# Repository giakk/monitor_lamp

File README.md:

# Monitor Light Bar

## Overview
I wanted a smart monitor bar without spending hundreds of euros for something like the BenQ monitor lamp, so I tried to DIY it. Everithing runs on an ESP32-C3 microcontroller, a bit overkill but it will be useful for future upgrade. To control the led, the ESP32 rely on two sensors: a VELM7700 luminosity sensor to dynamically adjusts the leds brightness to maintain optimal lighting conditions, and a LD2410 presense sensor to automatically activates when a user sits.

## 3D Design

## Electronics
The system is powered by a 12V input managed via a USB-C Power Delivery (PD) controller, which negotiate with the power supply to ensures 12V for the leds strips. A Mini360 step-down converter reduces this voltage to 5V to power the ESP32-C3 and the sensors, while a dedicated 1.25A fuse protects the entire circuit. The light engine consists of a 12V LED strip driven by an IRLZ44N MOSFET, which allows for precise PWM dimming controlled by the ESP32.

The "intelligence" of the hardware relies on two main modules: an LD2410 presence sensor connected via UART and a VEML7700 ambient light sensor communicating through the I2C protocol. 
The current prototype, as shown in the images below was updated with the new custom developed PCB board, which info can be found in the Kicad project. (Yeah, I know it is overkill but why no? I wanted to learn to use Kicad and develop my first PCB)

|  |  |
|:---:|:---:|

The board has been tested and corrected due to two mistakes I made in the eletrical scheme. First, I hadn't included the ISET resistor for the PD controller, which is essential for negotiating the correct voltage with the charger. Second, I had swapped the drain and source pins of the Q3 MOSFET. Now that everything works as expected, the board project should be correct I you want to produce it.

## Code
The firmware is developed within the Arduino framework and utilizes a non-blocking logic to monitor environmental changes in real-time. The core functionality revolves around an adaptive dimming algorithm: the system reads the ambient lux levels via the VEML7700 and applies a square root function to calculate the ideal LED duty cycle. This function actually work like the luminosity on the phone, so it increase if the lux of the room are high, while decrease if there is not light in the room. Maybe it is counterintuitive but it works for me. Change it as you want. 
To prevent annoying flickering or constant micro-adjustments, the code implements a hysteresis logic, only triggering a brightness transition if the change in light is significant. Furthermore, the integration with the LD2410 mmWave radar allows the lamp to manage power efficiently, executing smooth fade-in and fade-out transitions whenever a user enters or leaves the desk area, ensuring the light is only active when actually needed.
    
I am working on a version of the software which expose a web page to interact with the light in real time. In the meantime, I uploaded the version of the sketch that actually works the best, with is the `sketch_monitor_lamp_working.ino`

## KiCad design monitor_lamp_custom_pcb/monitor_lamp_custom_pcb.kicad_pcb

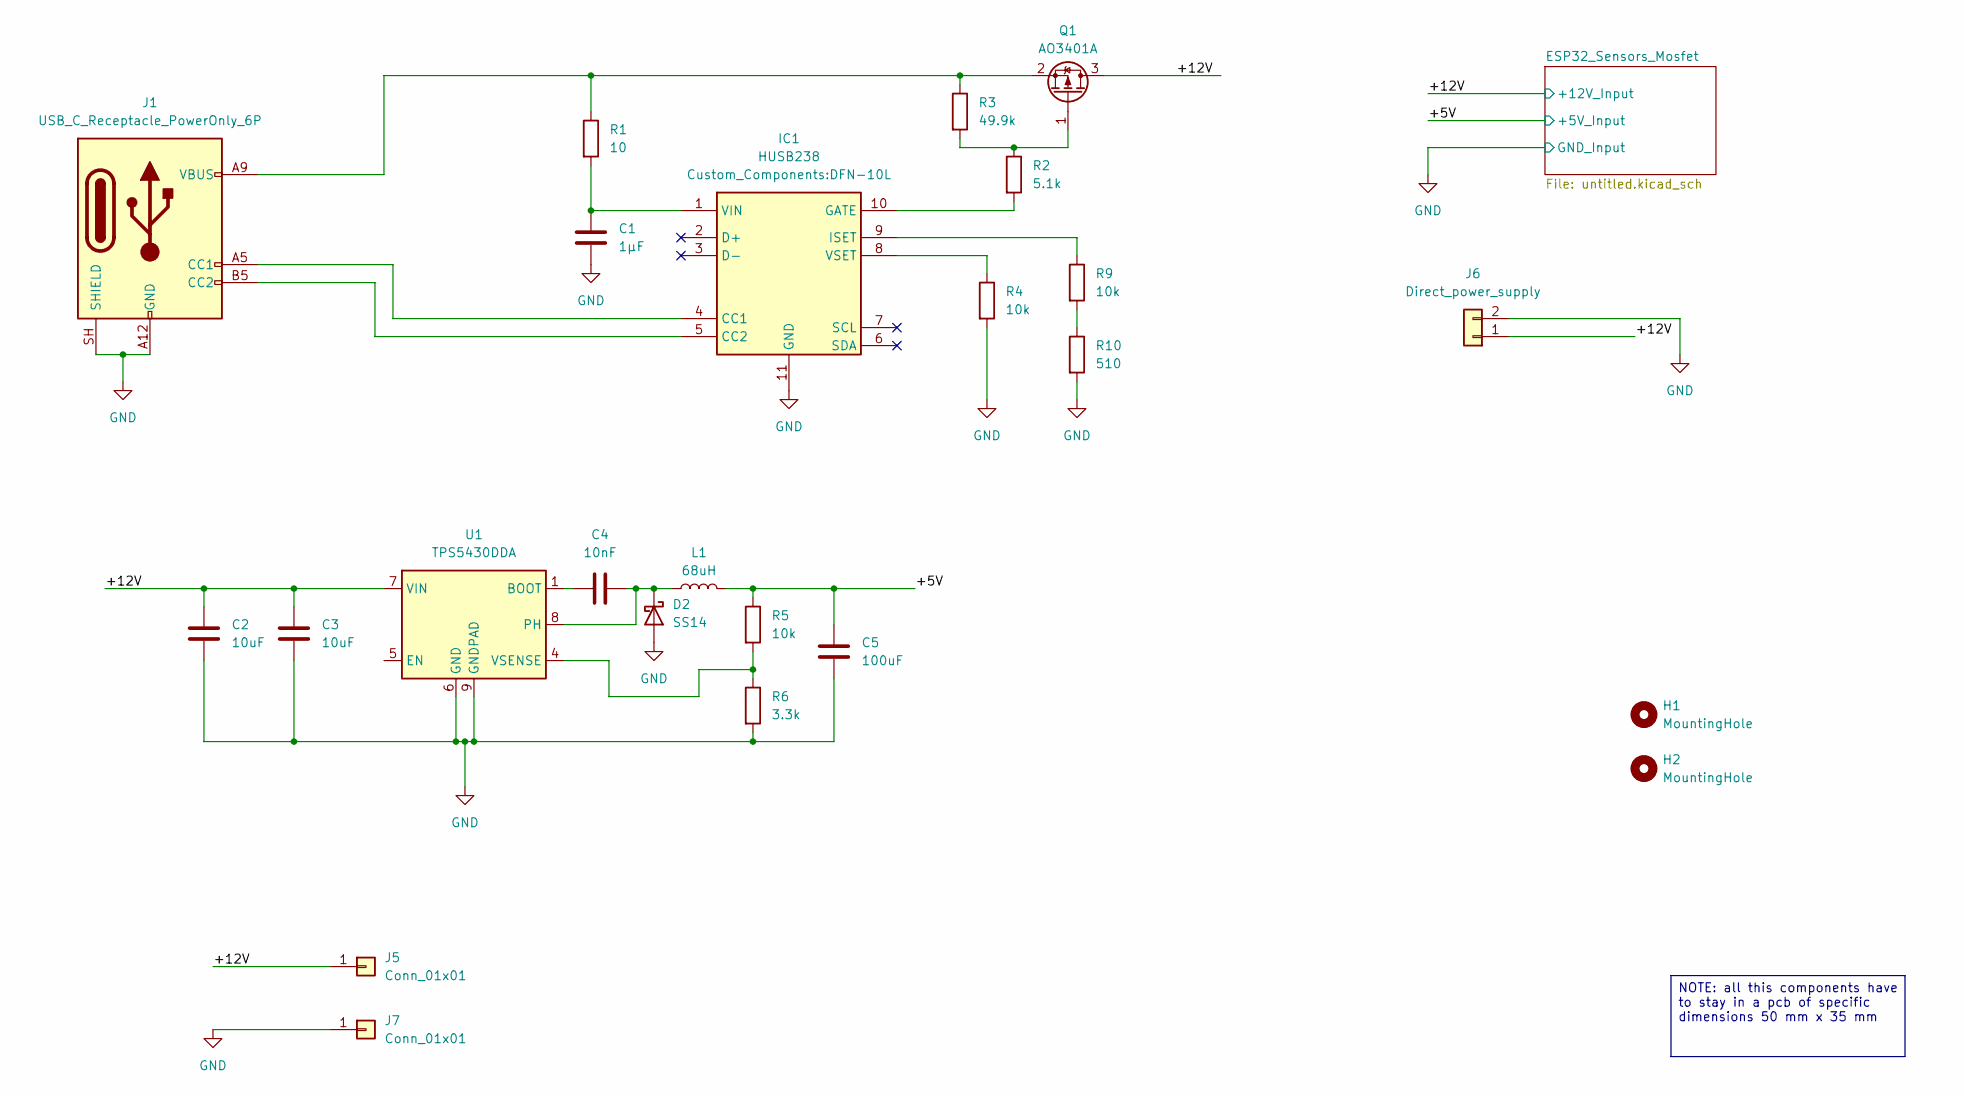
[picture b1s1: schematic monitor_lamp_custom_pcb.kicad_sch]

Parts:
C1: 1µF; C_0402_1005Metric; LCSC C52923
C2, C3: 10uF; C_0603_1608Metric; LCSC C96446
C4: 10nF; C_0402_1005Metric; LCSC C15195
C5: 100uF; CP_Elec_5x5.4
D2: SS14; D_SMA; LCSC C2480
H1, H2: MountingHole; MountingHole_2.2mm_M2
IC1: HUSB238; DFN-10L; Manufacturer_Part_Number HUSB238; LCSC C7471904
J1: USB_C_Receptacle_PowerOnly_6P; USB_C_Receptacle_GCT_USB4125-xx-x_6P_TopMnt_Horizontal; LCSC C283540
J5, J7: Conn_01x01; SolderWirePad_1x01_SMD_1.5x3mm
J6: Direct_power_supply
L1: 68uH; L_Sumida_CD75
Q1: AO3401A; SOT-23; LCSC C15127
R1: 10; R_0603_1608Metric; LCSC C22859
R2: 5.1k; R_0603_1608Metric; LCSC C23186
R3: 49.9k; R_0603_1608Metric; LCSC C23184
R4, R9: 10k; R_0402_1005Metric; LCSC C25744
R5: 10k; R_0603_1608Metric; LCSC C25804
R6: 3.3k; R_0603_1608Metric; LCSC C22978
R10: 510; R_0402_1005Metric; LCSC C25123
U1: TPS5430DDA; TI_SO-PowerPAD-8_ThermalVias; LCSC C9864

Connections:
/+5V: C5.1, L1.2, R5.1; also elsewhere on the board
/+12V: C2.1, C3.1, J5.1 (Pin_1_1), J6.1, Q1.3 (D), U1.7 (VIN); also elsewhere on the board
GND: C1.2, C2.2, C3.2, C5.2, D2.2 (A), IC1.11 (GND), J1.A12 (GND), J1.B12 (GND), J1.SH (SHIELD), J6.2, J7.1 (Pin_1_1), R4.2, R6.2, R10.2, U1.6 (GND), U1.9 (GNDPAD); also elsewhere on the board
unnamed: C4.2, D2.1 (K), L1.1, U1.8 (PH)
unnamed: IC1.4 (CC1), J1.A5 (CC1)
unnamed: IC1.5 (CC2), J1.B5 (CC2)
unnamed: IC1.10 (GATE), R2.2
unnamed: IC1.9 (ISET), R9.1
unnamed: C1.1, IC1.1 (VIN), R1.2
unnamed: IC1.8 (VSET), R4.1
unnamed: Q1.1 (G), R2.1, R3.2
unnamed: J1.A9 (VBUS), J1.B9 (VBUS), Q1.2 (S), R1.1, R3.1
unnamed: R9.2, R10.1
unnamed: C4.1, U1.1 (BOOT)
unnamed: R5.2, R6.1, U1.4 (VSENSE)

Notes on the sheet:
NOTE: all this components have to stay in a pcb of specific dimensions 50 mm x 35 mm

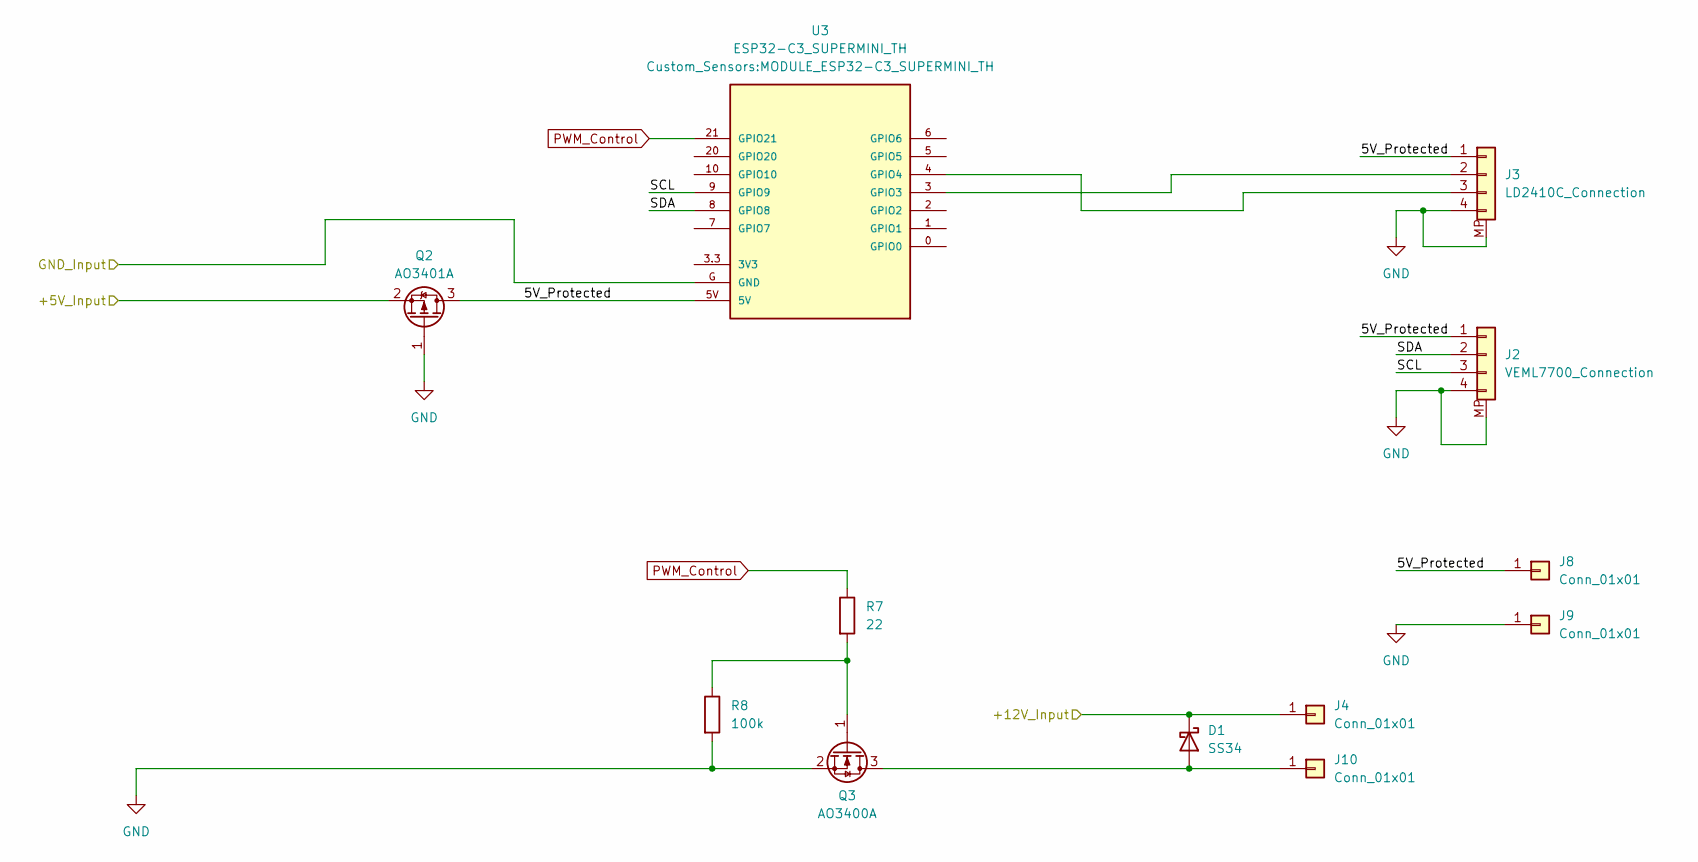
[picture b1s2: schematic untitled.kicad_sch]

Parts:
D1: SS34; D_SMA; LCSC C8678
J2: VEML7700_Connection; JST_PH_B4B-PH-K_1x04_P2.00mm_Vertical
J3: LD2410C_Connection; JST_PH_B4B-PH-K_1x04_P2.00mm_Vertical
J4, J8, J9, J10: Conn_01x01; SolderWirePad_1x01_SMD_1.5x3mm
Q2: AO3401A; SOT-23; LCSC C15127
Q3: AO3400A; SOT-23; LCSC C20917
R7: 22; R_0603_1608Metric; LCSC C23345
R8: 100k; R_0603_1608Metric; LCSC C25803
U3: ESP32-C3_SUPERMINI_TH; MODULE_ESP32-C3_SUPERMINI_TH

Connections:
/+5V: Q2.2 (S); also elsewhere on the board
/+12V: D1.1 (K), J4.1 (Pin_1_1); also elsewhere on the board
/ESP32_Sensors_Mosfet/5V_Protected: J2.1, J3.1, J8.1 (Pin_1_1), Q2.3 (D), U3.5V
/ESP32_Sensors_Mosfet/SCL: J2.3, U3.9 (GPIO9)
/ESP32_Sensors_Mosfet/SDA: J2.2, U3.8 (GPIO8)
GND: J2.4, J2.MP, J3.4, J3.MP, J9.1 (Pin_1_1), Q2.1 (G), Q3.2 (S), R8.2, U3.G (GND); also elsewhere on the board
unnamed: D1.2 (A), J10.1 (Pin_1_1), Q3.3 (D)
unnamed: J3.2, U3.3 (GPIO3)
unnamed: J3.3, U3.4 (GPIO4)
unnamed: Q3.1 (G), R7.2, R8.1
PWM_Control: R7.1, U3.21 (GPIO21)

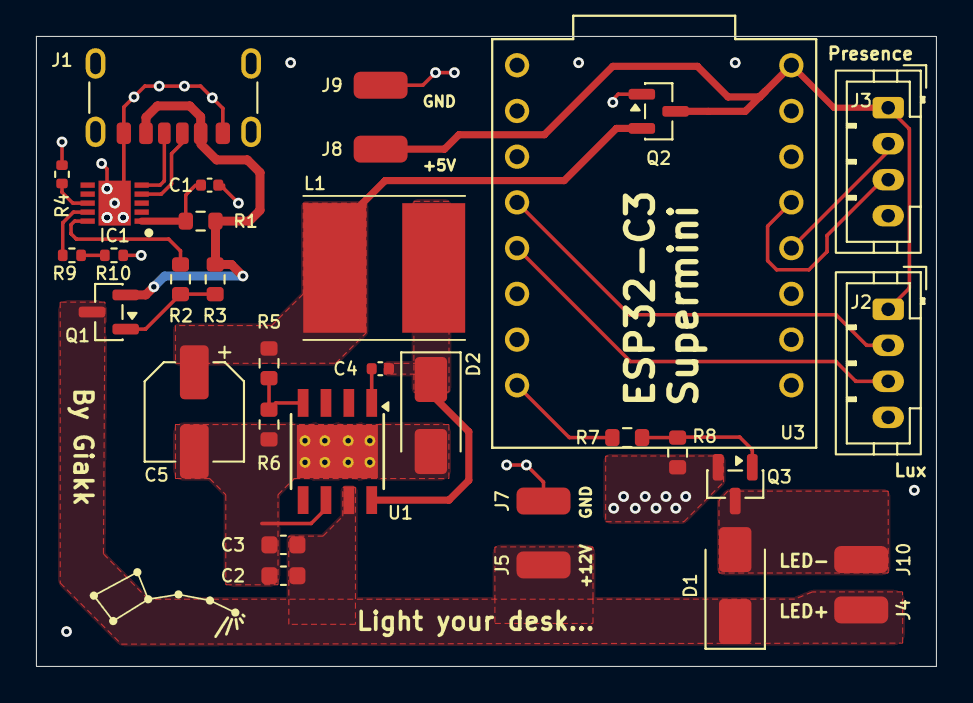
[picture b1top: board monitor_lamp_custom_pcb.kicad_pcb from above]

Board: 2 copper layers, 50.0 x 35.0 mm, 35 parts (0 on the bottom side), 23 nets.

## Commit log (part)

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2026-04-17 implemented fade using ledc library function
    Smoother effect
2026-04-18 Added custom library component to the project
    In Kicad not all components are present in the default library, some sensors or modules have to be manually added importing symbols and footprint.
    Putting this components inside the project is useful so if someone will download it, in is not necessary to search and import the components
2026-04-18 Started to place component in the pcb design.
2026-04-19 Started to place components on the board layout
2026-04-20 Added almost all components to the board. Next step trace
2026-04-20 Placed all components, changed the J2 & J3 connectors
2026-04-20 Modified layout and J2&J3 connectors
2026-04-20 Selected 4-Layer setup. Started to trace
2026-04-20 Tracing some routes
2026-04-21 Trace all routes and zone on pcb
2026-04-21 Added GND via around pcb area
2026-04-21 Added connection for temp sensor
2026-04-21 Added supplementary power supply connection
2026-04-22 Some test
2026-04-23 Corrected position and writing of graphical layer
2026-04-23 Minor changes
2026-04-24 Changed all resistors footprint to R_0603_1608 metric
2026-04-24 Added some LCSC to the components
2026-04-25 Assign LCSC number to some component and selected new voltage regulator
2026-04-27 Drastic change
2026-04-29 Remodelled the scheme with 12V input
2026-05-06 Placed connection pad
2026-05-06 Terminated design, generated fabrication files for JLCPCB
2026-05-06 almost done
2026-05-07 Added some drawing to the board and recreated fabbrication file
2026-05-07 Changed connector to JST PH 2.0mm
2026-05-08 Definitive version - Ordered on JLCPCB
2026-05-10 Added step model of the lamp
2026-05-11 Initialize README with project details and instructions
    Add detailed project overview, electronics, and code explanations.
2026-05-11 Added proto board photos
2026-05-11 Revise README file
2026-05-11 Added proto board circuit diagram
2026-05-11 Update README file
2026-05-13 Updated sketch_monitor_lamp.ino. Compiling but not tested
2026-05-22 Added ISET resistor for solving 12V issue on previous release
2026-06-04 Corrected ISET pin error and changed to pads for connecting LED supply
2026-06-04 Simplified ESP32 sketch (TO BE TESTED ON BOARD)
2026-06-05 Starting the implementation of web server for controlling the lamp
2026-06-19 Corrected bug with N-Mosfet
